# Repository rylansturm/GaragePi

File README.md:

# GaragePi

#### UPDATE 9/7/2023

About a month ago I got the case printed and everything mounted in my garage.
The sensors are IR prox sensors that sit just above the door when closed, but
the PCB can work with anything that has a 3.3V, GND, and Sensor pin configuration.
The wiring is a CAT5 cable terminated with an aviation plug on the Pi side and
screw terminals on the sensor side.

I can access the Pi remotely via SSH. I am now working on setting up an MQTT 
(Mosquitto) broker on my home network. Then I'll work on setting up an API and
GUI on my public server so remote access is more user friendly.

## Specs

#### Basic Requirements

Non-destructive. The project must not remove anything from the current
garage door system. Wires can be added into and below the physical 
buttons that are on the garage wall now. Disconnection should be easy.

Open/Close. A relay can be used to make the connection that send the
signal to the garage openers. 

Scalable. The system should support my two garage doors, and
should ideally be scalable up or down easily. One door without useless
clutter in the UI, 3 doors just as simply.

Sensors. I should be able to read the current state of the garage.

#### MVP

A minimum viable project is one where I can control my garage door
via ssh when connected to WiFi. That just means Raspberry Pi, 
Relay board, and a local bash script. Let's go.

#### UPDATE 3/20/2023

Minimum viable project is in place. I can now open and close garage doors
by running the rust script with argument '1' or '2'. Only from local network.
No monitoring system in place

#### UPDATE 6/26/2023

A PCB has been designed that will sit on top of the Pi.
It has been ordered and should be in place in the next week or so.
Now on to designing the sensors.

#### PCB Design

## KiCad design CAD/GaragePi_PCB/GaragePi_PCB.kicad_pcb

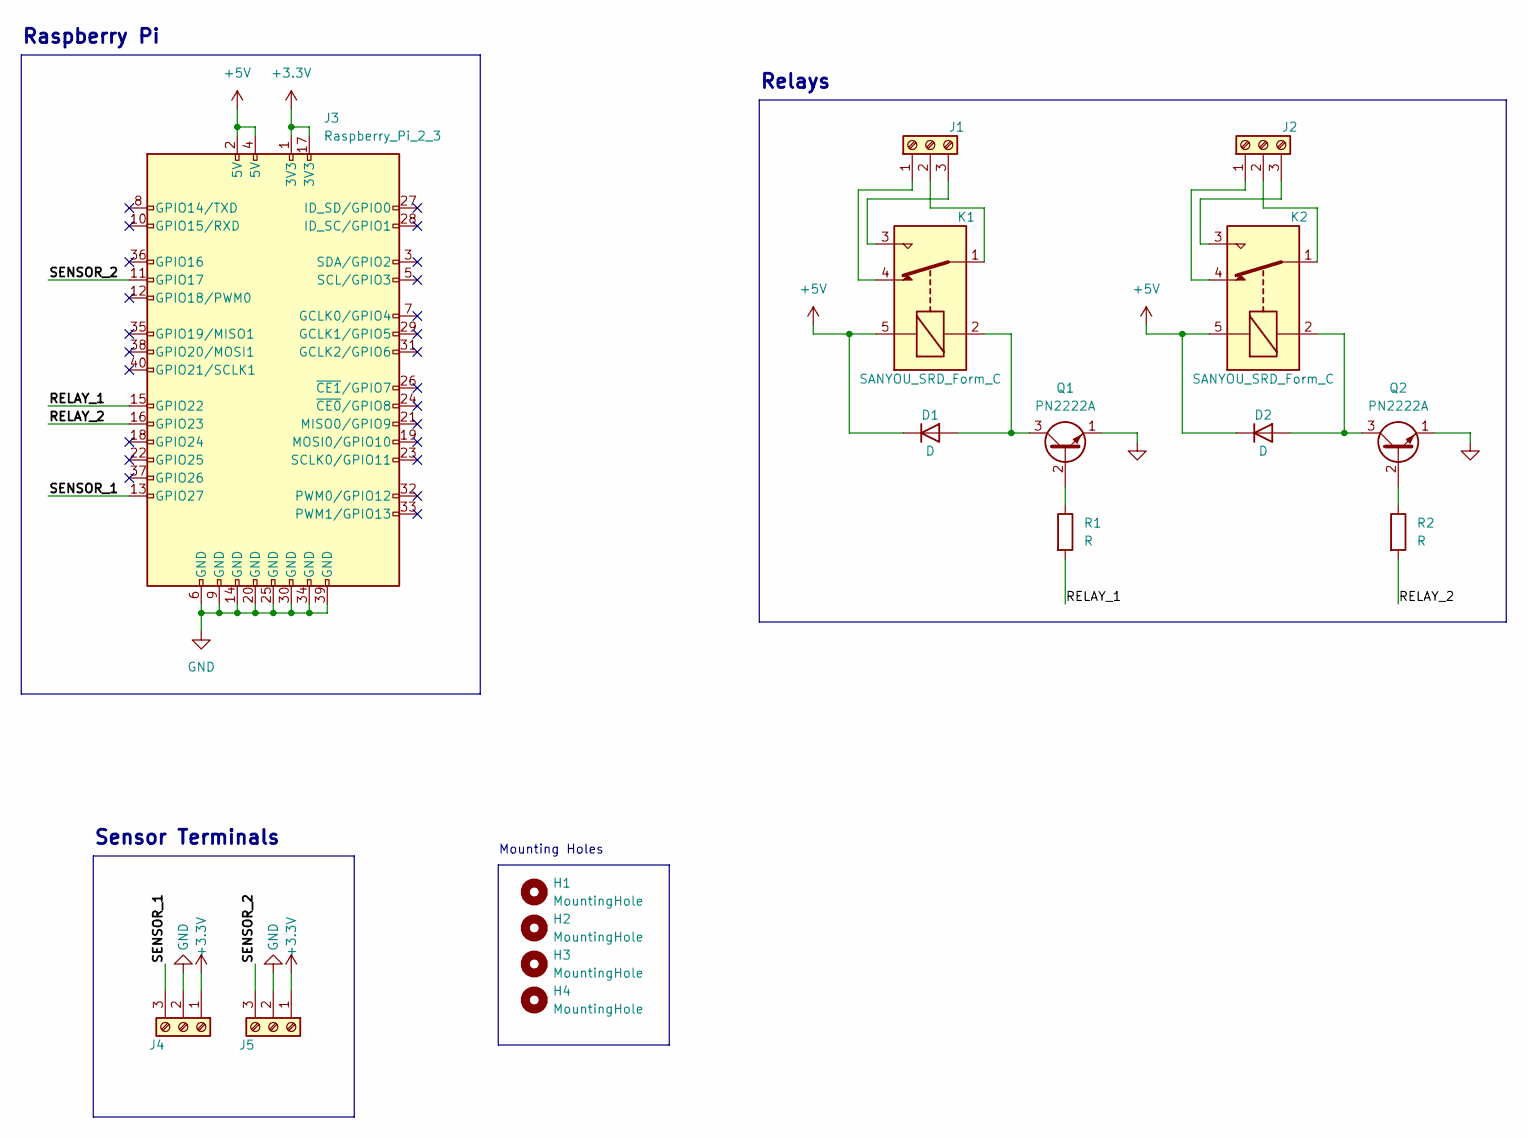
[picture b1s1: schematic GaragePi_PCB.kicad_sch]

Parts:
D1, D2: D; D_DO-35_SOD27_P3.81mm_Vertical_AnodeUp
H1, H2, H3, H4: MountingHole; MountingHole_2.7mm_M2.5
J1, J2, J4, J5: Screw_Terminal_01x03; TerminalBlock_RND_205-00013_1x03_P5.00mm_Horizontal
J3: Raspberry_Pi_2_3; PinSocket_2x20_P2.54mm_Vertical
K1, K2: SANYOU_SRD_Form_C; Relay_SPDT_SANYOU_SRD_Series_Form_C
Q1, Q2: PN2222A; TO-92_Inline
R1, R2: R; R_Axial_DIN0207_L6.3mm_D2.5mm_P7.62mm_Horizontal

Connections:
+3.3V: J3.1 (3V3), J3.17 (3V3), J4.1, J5.1
+5V: D1.1 (K), D2.1 (K), J3.2 (5V), J3.4 (5V), K1.5, K2.5
/RELAY_1: J3.15 (GPIO22), R1.2
/RELAY_2: J3.16 (GPIO23), R2.2
/SENSOR_1: J3.13 (GPIO27), J4.3
/SENSOR_2: J3.11 (GPIO17), J5.3
GND: J3.6 (GND), J3.9 (GND), J3.14 (GND), J3.20 (GND), J3.25 (GND), J3.30 (GND), J3.34 (GND), J3.39 (GND), J4.2, J5.2, Q1.1 (E), Q2.1 (E)
unnamed: D1.2 (A), K1.2, Q1.3 (C)
unnamed: D2.2 (A), K2.2, Q2.3 (C)
unnamed: J1.1, K1.4
unnamed: J1.2, K1.1
unnamed: J1.3, K1.3
unnamed: J2.1, K2.4
unnamed: J2.2, K2.1
unnamed: J2.3, K2.3
unnamed: Q1.2 (B), R1.1
unnamed: Q2.2 (B), R2.1

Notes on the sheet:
Mounting Holes
Sensor Terminals
Raspberry Pi
Relays

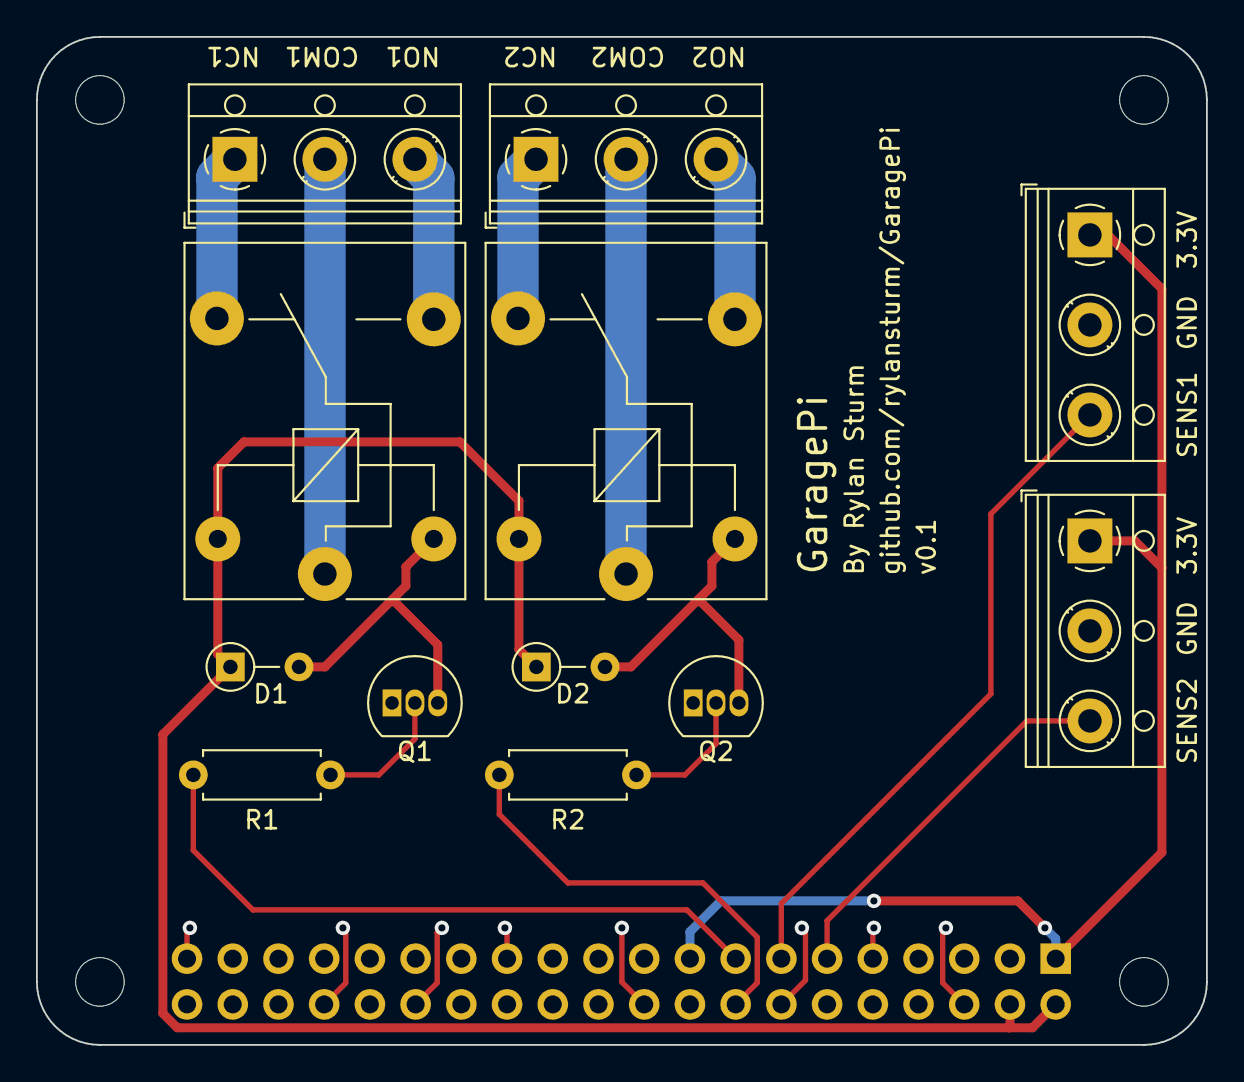
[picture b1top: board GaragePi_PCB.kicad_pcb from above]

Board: 2 copper layers, 65.0 x 56.0 mm, 17 parts (1 on the bottom side), 17 nets.

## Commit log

2023-01-31 readme
2023-02-02 garageOpener.py, run.sh, and .gitignore
2023-02-06 Added gpio control in garageOpener.py
2023-02-06 Added pin functionality
2023-03-12 added v0.1 of the baseplate
2023-03-12 Fixed hole width on relay mount
2023-03-21 made rust file for running garage door
2023-03-21 no longer using python for controlling relays
2023-03-21 Update README.md
    Updated progress for 3/20/2023
2023-04-15 added requirements
2023-04-16 portfolio page at MVP
2023-04-18 server is live
2023-04-18 added about me
2023-04-19 removed link to private repo
2023-04-20 removed login link, added github-mark
2023-04-22 changed EOL in vscode
2023-04-24 added background
2023-04-24 backgroundImage
2023-05-09 Added info to /index and added background image; Added /contact; Added footer; Added custom css file;
2023-05-11 Added pictures on index page; Added WIP note on Portfolio page;
2023-05-13 added background photo to contact page
2023-05-13 radius on images, no shadow on hero
2023-05-14 updated to bootstrap 5 using bootstrap-flask instead of flask-bootstrap; Added icons and logos
2023-05-14 added bootstrap-flask to requirements.txt
2023-05-14 changed css to 0.2
2023-05-14 larger hero image; larger index images; aligned text boxes; grayish background; removed final index text box and replaced with <p> and <btn> to make it cleaner;
2023-05-14 changed styles version to 0.3
2023-05-14 added Visit table and tracking of links being clicked
2023-05-15 added timestamp to visit table
2023-05-15 fixed title issue from migrating to bootstrap5
2023-05-15 fixed render_form bug from migrating to bootstrap5
2023-06-26 added kicad files v0.1
2023-06-27 completed PCB schematics v0.1; Updated README with the project update
2023-06-27 Added img folder and pcbv0.1.png
2023-07-06 modeled buttons; Started housing for GaragePi
2023-07-06 first printable GaragePi housing
2023-07-08 modified GaragePi_Housing to accomodate sd card and so hinge aligned
2023-07-10 working Rust script. Needs validation and error handling
2023-07-10 added argument validation and error messages in Rust script
2023-10-03 restructured directory
2023-10-31 added MVP garage functionality
